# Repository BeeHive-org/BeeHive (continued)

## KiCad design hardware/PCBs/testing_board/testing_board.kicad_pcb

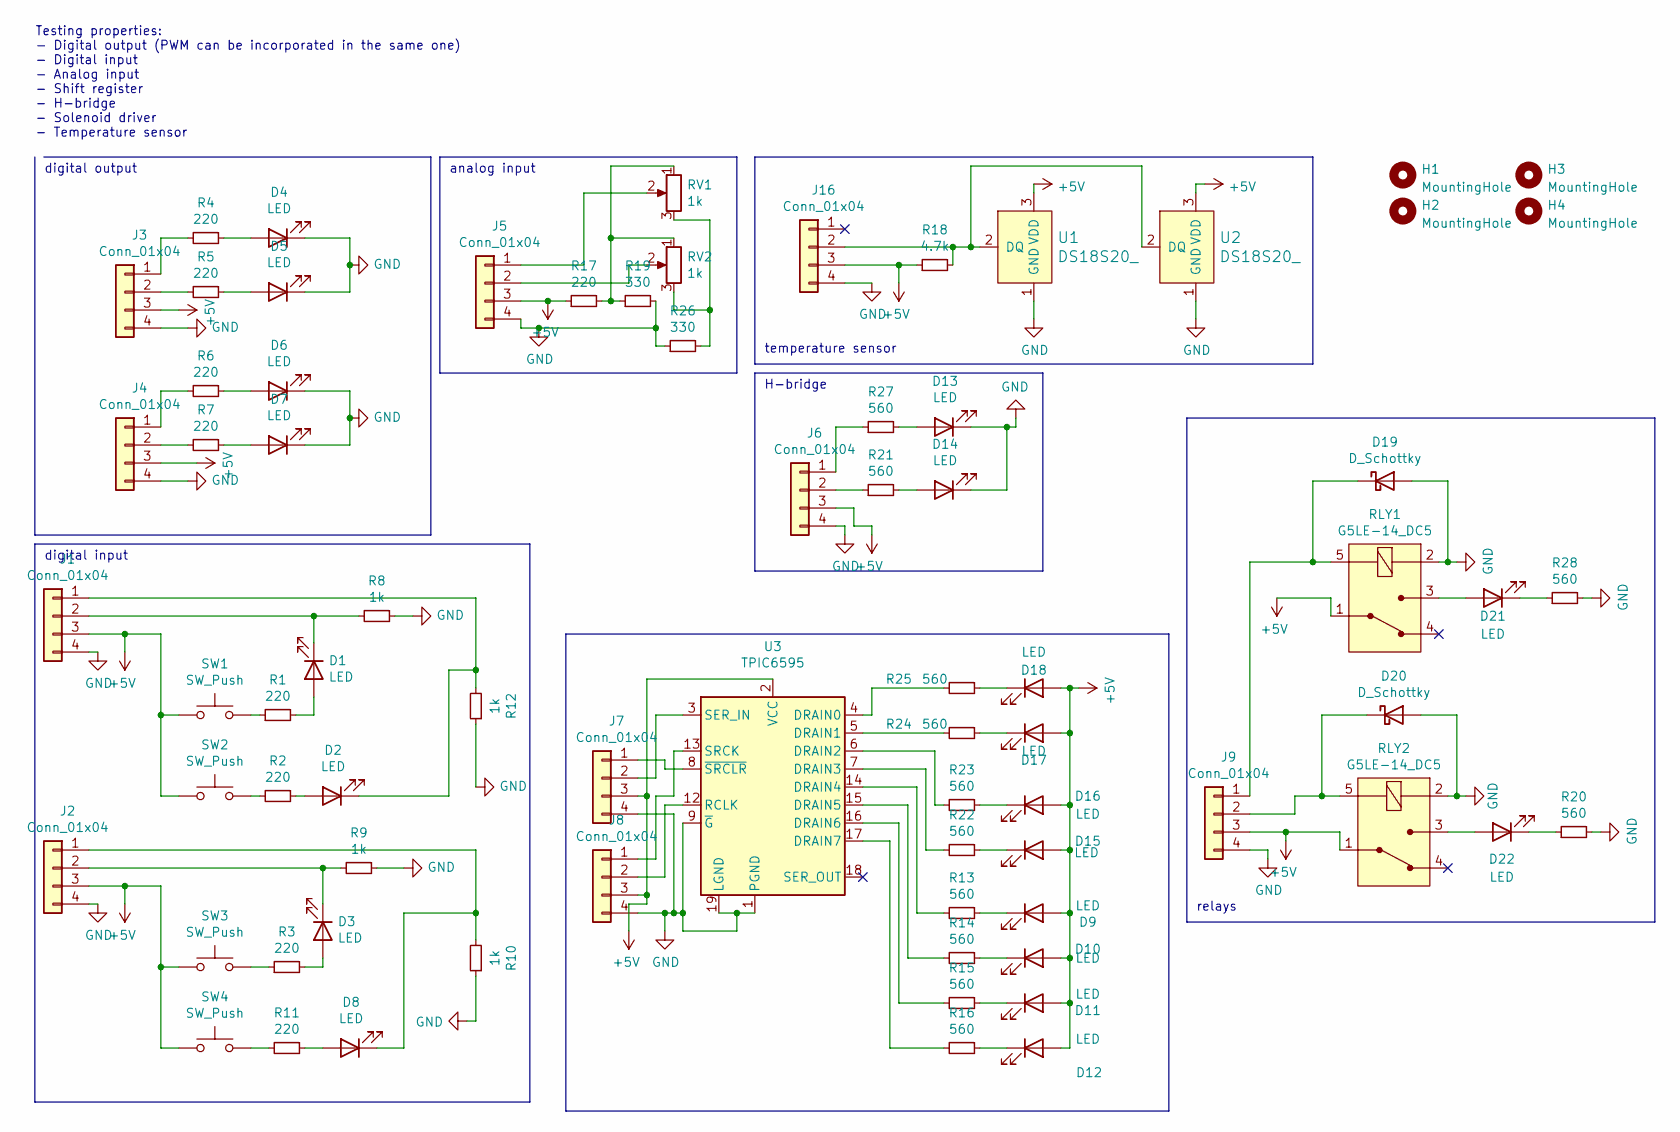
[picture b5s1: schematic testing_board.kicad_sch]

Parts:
D1, D2, D3, D4, D5, D6, D7, D8, D9, D10, D11, D12, D13, D14, D15, D16, D17, D18, D21, D22: LED; LED_D3.0mm
D19, D20: D_Schottky; D_DO-201AE_P15.24mm_Horizontal
H1, H2, H3, H4: MountingHole; MountingHole_3.2mm_M3_DIN965
J1, J2, J3, J4, J5, J6, J7, J8, J9, J16: Conn_01x04; JST_XH_B4B-XH-A_1x04_P2.50mm_Vertical
R1, R2, R3, R4, R5, R6, R7, R11, R17: 220; R_Axial_DIN0204_L3.6mm_D1.6mm_P2.54mm_Vertical
R8, R9, R10, R12: 1k; R_Axial_DIN0204_L3.6mm_D1.6mm_P2.54mm_Vertical
R13, R14, R15, R16, R20, R21, R22, R23, R24, R25, R27, R28: 560; R_Axial_DIN0204_L3.6mm_D1.6mm_P2.54mm_Vertical
R18: 4.7k; R_Axial_DIN0204_L3.6mm_D1.6mm_P2.54mm_Vertical
R19, R26: 330; R_Axial_DIN0204_L3.6mm_D1.6mm_P2.54mm_Vertical
RLY1, RLY2: G5LE-14_DC5; Relay_THT_G5LE-14; MPN G5LE-14 DC5; Digi-Key_PN Z1011-ND
RV1, RV2: 1k; Potentiometer_Alps_RK09K_Single_Vertical
SW1, SW2, SW3, SW4: SW_Push; SW_PUSH_6mm
U1, U2: DS18S20_; TO-92-3; MPN DS18S20+; Digi-Key_PN DS18S20+-ND
U3: TPIC6595; DIP-20_W7.62mm_LongPads

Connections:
+5V: D9.2 (A), D10.2 (A), D11.2 (A), D12.2 (A), D15.2 (A), D16.2 (A), D17.2 (A), D18.2 (A), J1.3, J2.3, J3.3, J4.3, J5.3, J6.3, J7.3, J8.3, J9.3, J16.3, R17.1, R18.1, RLY1.1 (COM), RLY2.1 (COM), SW1.1, SW2.1, SW3.1, SW4.1, U1.3 (VDD), U2.3 (VDD), U3.2 (VCC)
GND: D4.1 (K), D5.1 (K), D6.1 (K), D7.1 (K), D13.1 (K), D14.1 (K), D19.2 (A), D20.2 (A), J1.4, J2.4, J3.4, J4.4, J5.4, J6.4, J7.4, J8.4, J9.4, J16.4, R8.1, R9.1, R10.1, R12.1, R19.2, R20.2, R26.1, R28.2, RLY1.2 (COIL), RLY2.2 (COIL), U1.1 (GND), U2.1 (GND), U3.1 (PGND), U3.9 (~G), U3.10 (PGND), U3.11 (PGND), U3.19 (LGND), U3.20 (PGND)
unnamed: D1.1 (K), J1.2, R8.2
unnamed: D1.2 (A), R1.2
unnamed: D2.1 (K), J1.1, R12.2
unnamed: D2.2 (A), R2.1
unnamed: D3.1 (K), J2.2, R9.2
unnamed: D3.2 (A), R3.2
unnamed: D4.2 (A), R4.1
unnamed: D5.2 (A), R5.1
unnamed: D6.2 (A), R6.1
unnamed: D7.2 (A), R7.1
unnamed: D8.1 (K), J2.1, R10.2
unnamed: D8.2 (A), R11.1
unnamed: D9.1 (K), R13.1
unnamed: D11.1 (K), R15.1
unnamed: D13.2 (A), R27.2
unnamed: D14.2 (A), R21.2
unnamed: D15.1 (K), R22.1
unnamed: D16.1 (K), R23.1
unnamed: D17.1 (K), R24.1
unnamed: D19.1 (K), J9.1, RLY1.5 (COIL)
unnamed: D20.1 (K), J9.2, RLY2.5 (COIL)
unnamed: D21.1 (K), R28.1
unnamed: D21.2 (A), RLY1.3 (NO)
unnamed: D22.1 (K), R20.1
unnamed: D22.2 (A), RLY2.3 (NO)
unnamed: J3.1, R4.2
unnamed: J3.2, R5.2
unnamed: J4.1, R6.2
unnamed: J4.2, R7.2
unnamed: J5.1, RV1.2
unnamed: J5.2, RV2.2
unnamed: J6.1, R27.1
unnamed: J6.2, R21.1
unnamed: J7.1, U3.8 (~SRCLR)
unnamed: J7.2, U3.3 (SER_IN)
unnamed: J8.1, U3.13 (SRCK)
unnamed: J8.2, U3.12 (RCLK)
unnamed: J16.2, R18.2, U1.2 (DQ), U2.2 (DQ)
unnamed: R1.1, SW1.2
unnamed: R2.2, SW2.2
unnamed: R3.1, SW3.2
unnamed: R11.2, SW4.2
unnamed: D10.1 (K), R14.1
unnamed: D12.1 (K), R16.1
unnamed: R17.2, R19.1, RV1.1, RV2.1
unnamed: R24.2, U3.5 (DRAIN1)
unnamed: D18.1 (K), R25.1
unnamed: R26.2, RV1.3, RV2.3
unnamed: R25.2, U3.4 (DRAIN0)
unnamed: R23.2, U3.6 (DRAIN2)
unnamed: R22.2, U3.7 (DRAIN3)
unnamed: R13.2, U3.14 (DRAIN4)
unnamed: R14.2, U3.15 (DRAIN5)
unnamed: R15.2, U3.16 (DRAIN6)
unnamed: R16.2, U3.17 (DRAIN7)

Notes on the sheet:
digital output
analog input
Testing properties: - Digital output (PWM can be incorporated in the same one) - Digital input - Analog input - Shift register - H-bridge - Solenoid driver - Temperature sensor
H-bridge
relays
digital input
temperature sensor

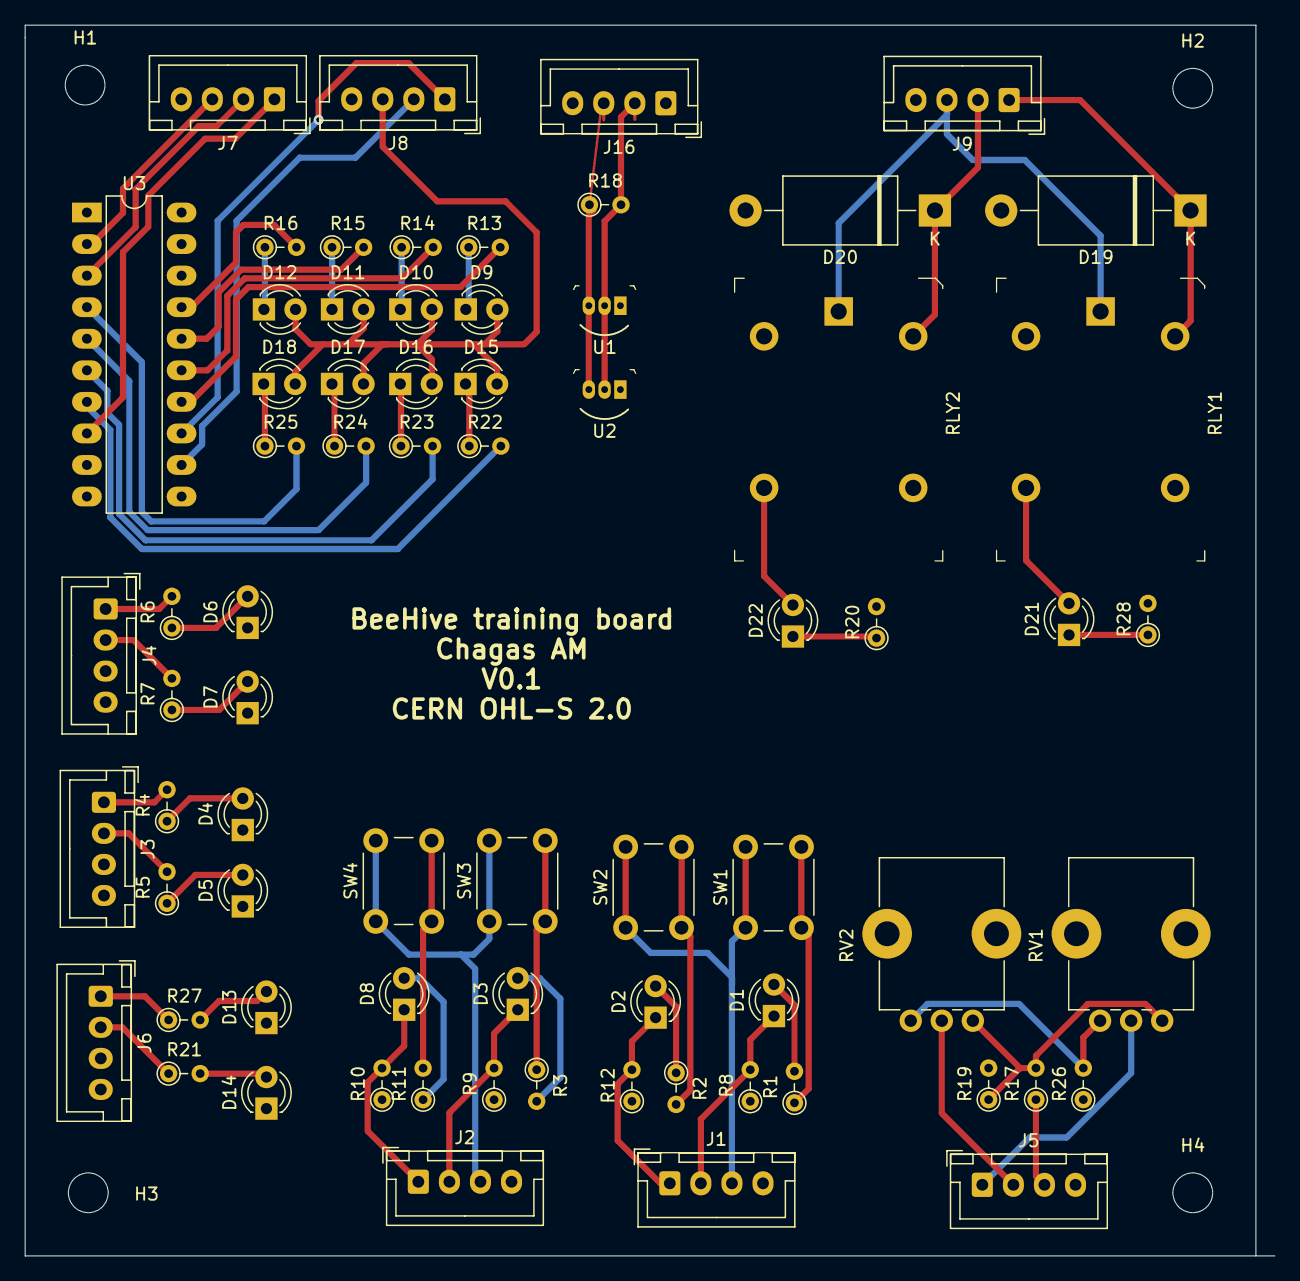
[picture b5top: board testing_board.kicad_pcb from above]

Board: 2 copper layers, 100.6 x 99.1 mm, 75 parts (0 on the bottom side), 57 nets.

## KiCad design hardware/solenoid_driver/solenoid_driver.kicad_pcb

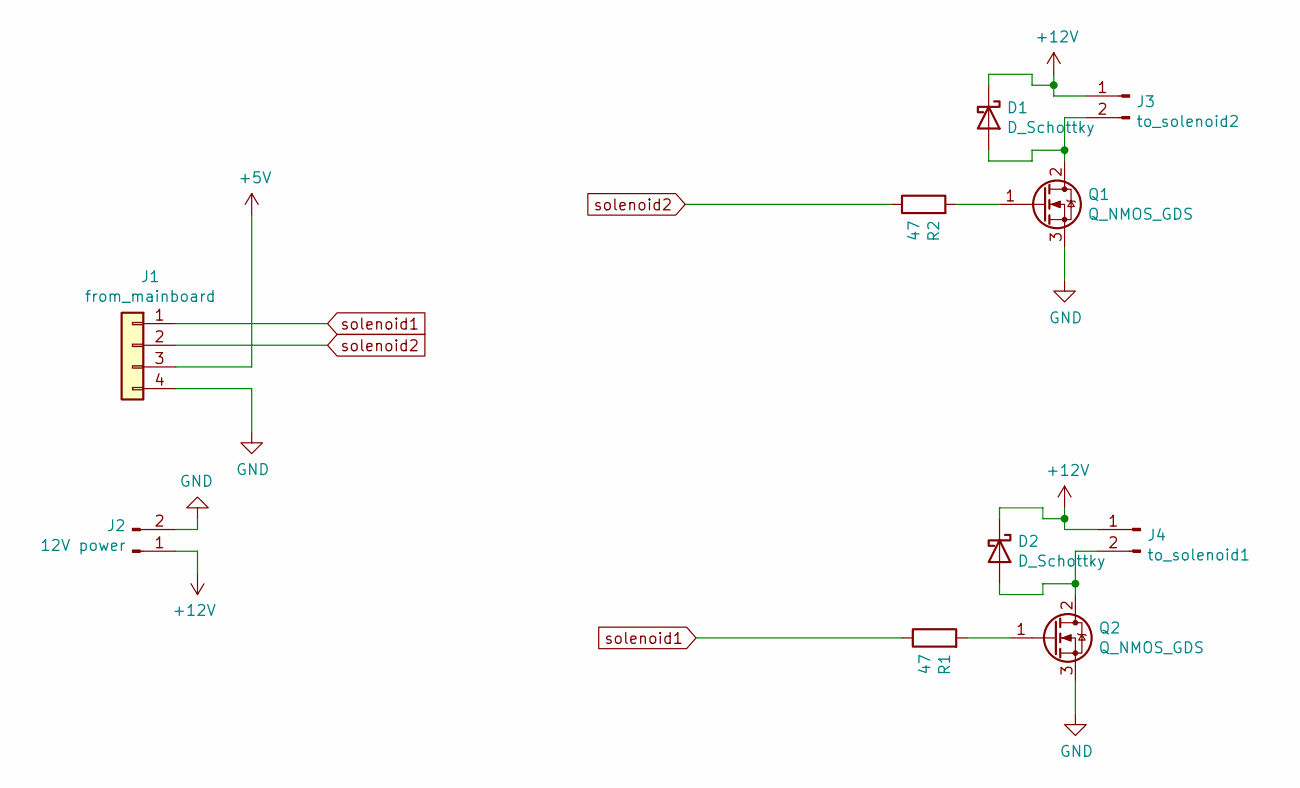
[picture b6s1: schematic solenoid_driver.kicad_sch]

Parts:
D1, D2: D_Schottky; D_DO-201AD_P15.24mm_Horizontal
J1: from_mainboard; JST_XH_B4B-XH-A_1x04_P2.50mm_Vertical
J2: 12V power; JST_XH_B2B-XH-A_1x02_P2.50mm_Vertical
J3: to_solenoid2; JST_XH_B2B-XH-A_1x02_P2.50mm_Vertical
J4: to_solenoid1; JST_XH_B2B-XH-A_1x02_P2.50mm_Vertical
Q1, Q2: Q_NMOS_GDS; TO-220-3_Vertical
R1, R2: 47; R_Box_L13.0mm_W4.0mm_P9.00mm

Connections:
+5V: J1.3
+12V: D1.1 (K), D2.1 (K), J2.1, J3.1, J4.1
GND: J1.4, J2.2, Q1.3 (S), Q2.3 (S)
unnamed: D1.2 (A), J3.2, Q1.2 (D)
unnamed: D2.2 (A), J4.2, Q2.2 (D)
unnamed: Q1.1 (G), R2.2
unnamed: Q2.1 (G), R1.2
solenoid1: J1.1, R1.1
solenoid2: J1.2, R2.1

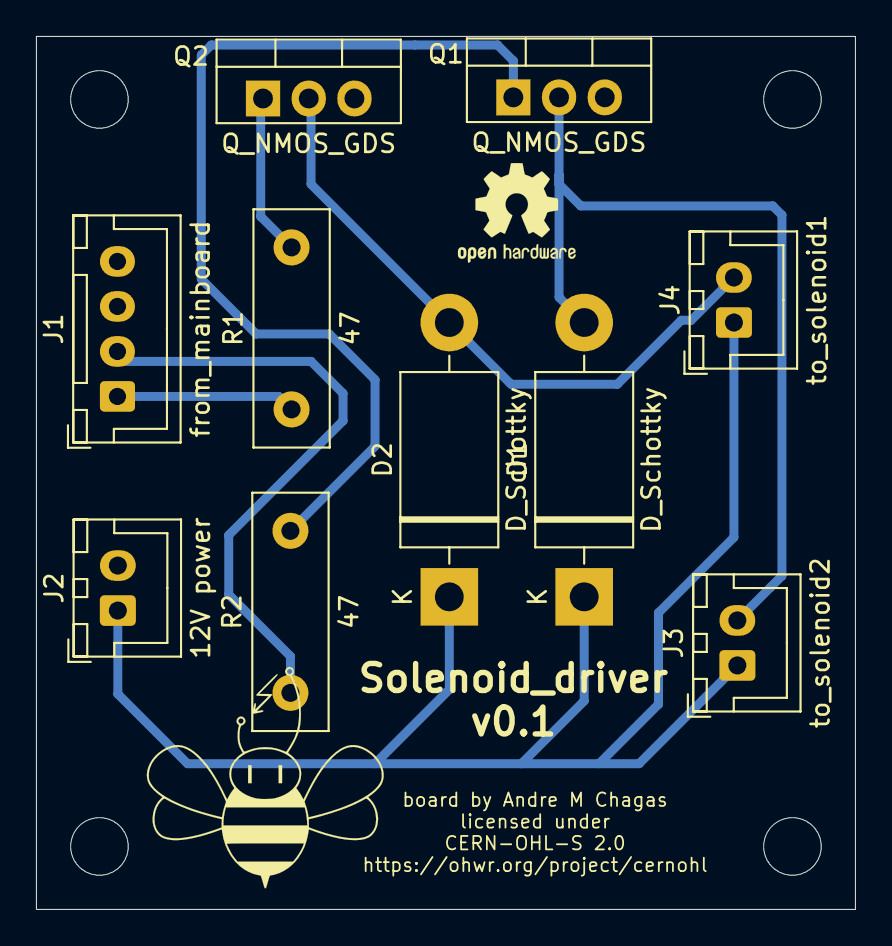
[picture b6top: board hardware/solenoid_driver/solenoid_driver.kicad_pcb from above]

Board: 2 copper layers, 45.5 x 48.5 mm, 10 parts (0 on the bottom side), 8 nets.

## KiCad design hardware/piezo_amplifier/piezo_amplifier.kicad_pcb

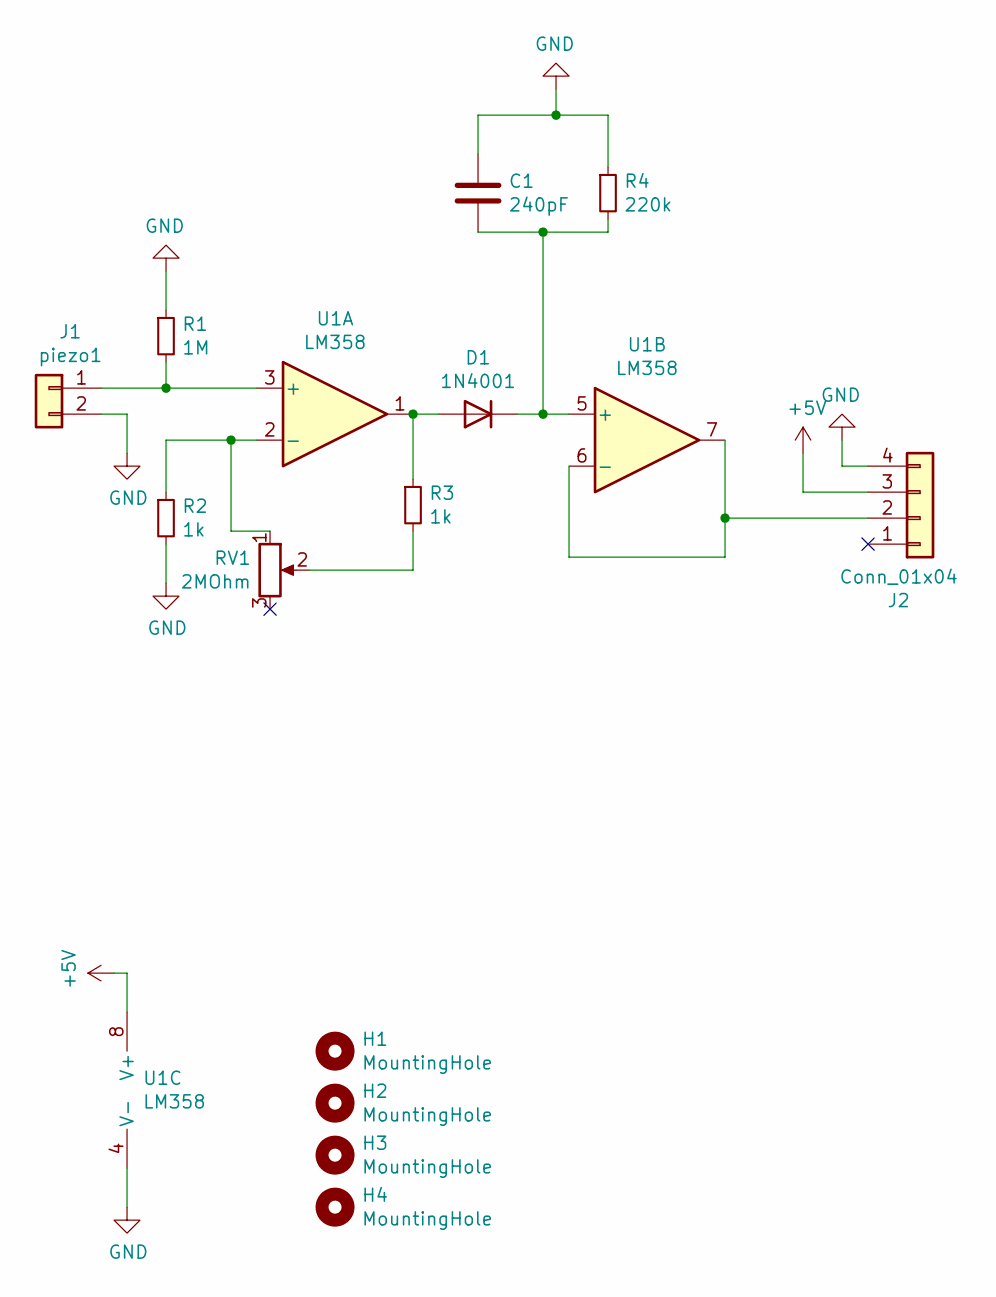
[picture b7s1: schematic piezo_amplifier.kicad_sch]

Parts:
C1: 240pF; C_Disc_D4.7mm_W2.5mm_P5.00mm
D1: 1N4001; D_DO-41_SOD81_P10.16mm_Horizontal
H1, H2, H3, H4: MountingHole; MountingHole_3.2mm_M3_ISO7380
J1: piezo1; JST_XH_B2B-XH-A_1x02_P2.50mm_Vertical
J2: Conn_01x04; JST_XH_B4B-XH-A_1x04_P2.50mm_Vertical
R1: 1M; R_Axial_DIN0204_L3.6mm_D1.6mm_P5.08mm_Vertical
R2, R3: 1k; R_Axial_DIN0204_L3.6mm_D1.6mm_P5.08mm_Vertical
R4: 220k; R_Axial_DIN0204_L3.6mm_D1.6mm_P5.08mm_Vertical
RV1: 2MOhm; JST_XH_B3B-XH-A_1x03_P2.50mm_Vertical
U1: LM358; DIP-8_W7.62mm_LongPads

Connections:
+5V: J2.3, U1.8 (V+)
GND: C1.1, J1.2, J2.4, R1.1, R2.2, R4.1, U1.4 (V-)
unnamed: C1.2, D1.1 (K), R4.2, U1.5 (+)
unnamed: D1.2 (A), R3.1, U1.1
unnamed: J1.1, R1.2, U1.3 (+)
unnamed: J2.2, U1.6 (-), U1.7
unnamed: R2.1, RV1.1, U1.2 (-)
unnamed: R3.2, RV1.2

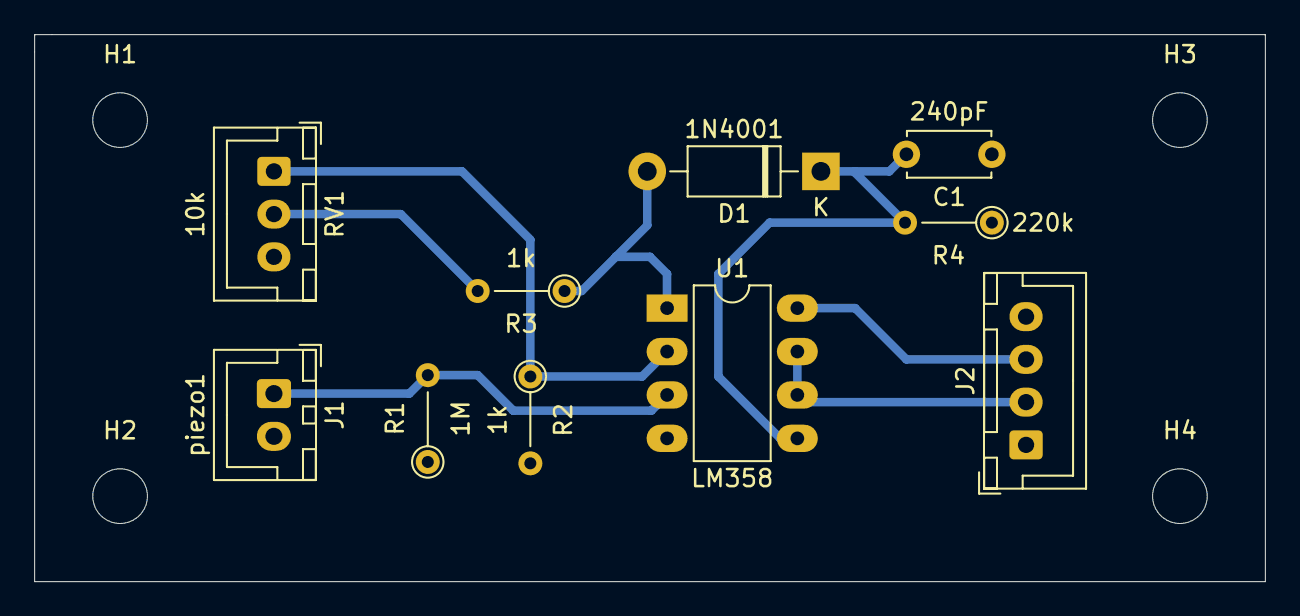
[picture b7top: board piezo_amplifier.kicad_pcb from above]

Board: 2 copper layers, 72.0 x 32.0 mm, 14 parts (0 on the bottom side), 8 nets.

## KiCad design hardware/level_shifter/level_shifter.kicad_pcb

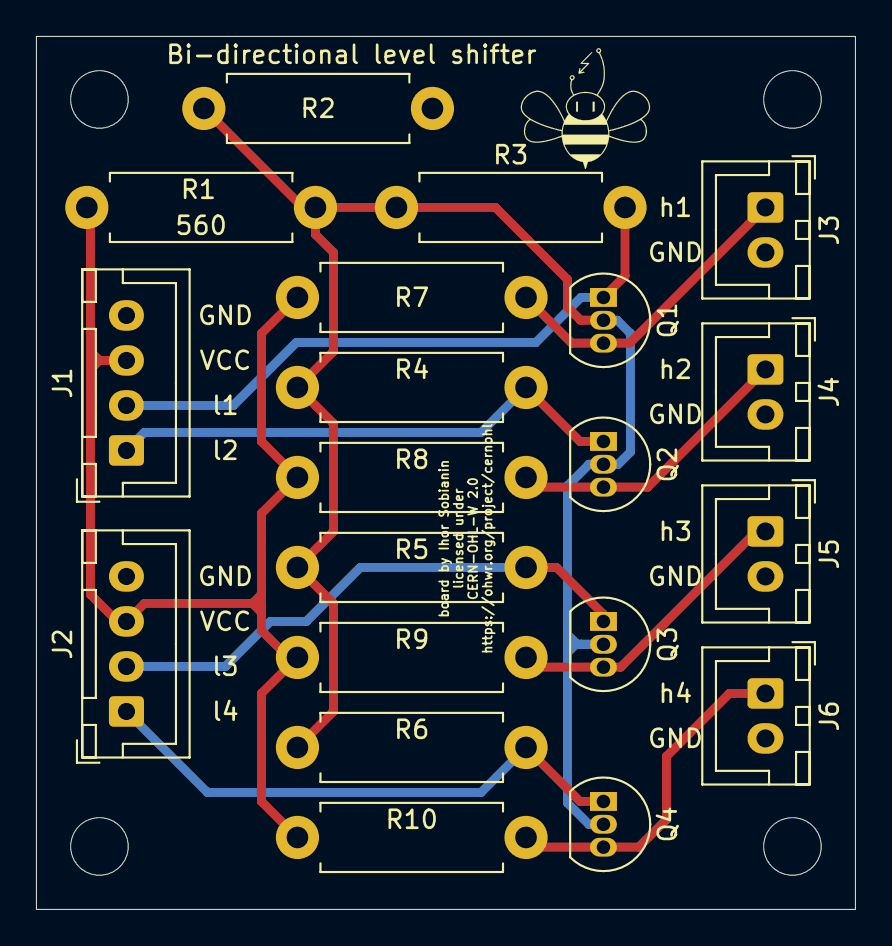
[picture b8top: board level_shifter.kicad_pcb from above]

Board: 2 copper layers, 45.5 x 48.5 mm, 20 parts (0 on the bottom side), 11 nets.

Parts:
J1, J2: Conn_01x04; JST_XH_B4B-XH-A_1x04_P2.50mm_Vertical
J3, J4, J5, J6: Conn_01x02; JST_XH_B2B-XH-A_1x02_P2.50mm_Vertical
Q1, Q2, Q3, Q4: 2N7000; TO-92_Inline
R1: 560; R_Axial_DIN0411_L9.9mm_D3.6mm_P12.70mm_Horizontal
R2, R3, R4, R5, R6, R7, R8, R9, R10: 1k; R_Axial_DIN0411_L9.9mm_D3.6mm_P12.70mm_Horizontal

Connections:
+3V3: Q1.2, Q2.2, Q3.2, Q4.2, R1.1, R2.2, R3.1, R4.1, R5.1, R6.1
+5V: J1.3, J2.3, R1.2, R7.1, R8.1, R9.1, R10.1
GND: J1.4, J2.4, J3.2, J4.2, J5.2, J6.2, R2.1
d1_h: J3.1, Q1.3, R7.2
d1_l: J1.2, Q1.1, R3.2
d2_h: J4.1, Q2.3, R8.2
d2_l: J1.1, Q2.1, R4.2
d3_h: J5.1, Q3.3, R9.2
d3_l: J2.2, Q3.1, R5.2
d4_h: J6.1, Q4.3, R10.2
d4_l: J2.1, Q4.1, R6.2

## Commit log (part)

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2019-11-17 add bare minimum readme
2019-11-17 Create LICENSE
2020-01-16 Schematics for the hub
2020-01-16 PCB file and cache library for schematics
2020-01-16 Other components from FlyPi
2020-01-16 The footprint for the ESP32 DevKit V2
2020-01-17 Gerber files for manufacturing
2020-01-17 Now Kitspace shows PCB correctly
    I could not figure out why the PCB was yellow. All zones were filled with yellow and the silk text was not visible. Looked horrible. However, other viewers worked correctly (used oshpark.com viewer).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
2020-01-23 Added more information regarding connector pinout
2020-01-25 Changed pinout to VCC-GND
2020-06-04 initial explanation on task
2020-06-04 correct bullet points
2020-06-04 finish first draft of the readme for software
2020-06-04 first micropython implementation
2020-06-05 more work on the microcontroller code, and open sound comm
2020-06-11 more software testing, and adding libraries
2020-06-11 organize folders
2020-06-12 work a bit on pin documentation
2020-06-15 more work on basis code
2020-06-16 first working version with output from ESP32 to Bonsai. Digital inputs only
2020-06-29 Redesigned version of the main hub
2020-06-30 work on documentation and on the first task (at the moment designed for the olfactory stimulator)
2020-07-13 more work on serial comm and the olfactory stimulator
2020-07-20 update code with more generic classes
    Instead of creating classes for each use case, we should add "generic" classes that different users can easily adapt for their own use cases.
2020-07-20 more work on base code
2020-07-21 blacken the code style and work on tasks
2020-07-21 solved tasks bugs
2020-07-21 re order repo and add bonsai min example
2020-08-21 update power supply
2020-08-21 move older board versions to archive folder
2020-08-21 update temp/humid sensor
2020-08-21 update gas sensor
2020-08-21 update v3 4 switch array
2020-08-21 update central hub silk --> channel names
2020-09-28 update 1-click boms
2020-10-16 Update PCB files
2020-10-17 Update silk layer
2020-10-18 Add custom libraries
    Add custom schematic symbols, footprints and 3D models
2020-10-18 Quick pinout fix for Peltier driver
    Simple fix with pinout now being correct
2020-11-06 New PID code for testing
    Added new PID control based on Arduino Python code
2020-12-04 update temperature sensor code, add another PID sample and add test code
2020-12-04 update test code
2020-12-09 more work on the PID controller. refactored Ihor's code so that it is a class and it does not need arrays to work.
2020-12-11 Update on 12V5A system power line
    - 12V5A power line is now represented by two connectors with 2 pins across all the modules
    - all .png previews are updated. The central hub now has previews for schematics, PCB tracing and 3D model
    - peltier module now has two 12V5A connectors with redesigned one side of the bridge. Now all MOSFETs can be equipped with heatsinks
    - hum/temp sensor now has its connector position reversed to mimic Grove's one
    - hum/temp and gas sensors now have a small BeeHive logo on front layer rather than one big on back layer
    - hum/temp sensor now use only one layer for signals and one layer for ground
2020-12-17 Add high power LED switch draft
    A rough draft of what is coming. The schematics includes MOSFETS with drivers and all complementary components
2020-12-19 Add high power switch and change 4 switch array
    - added high power switch
    - removed shift register from 4 switch array
    - changed some references on silk layer
    - small changes in switch arrays' tracing (width and paths)
2021-02-20 Add version number to boards
    Add version number to boards and update screenshots, zip gerber archives
2021-04-14 add yaml file to add boards to kitspace. starting with four boards for testing
2021-04-14 add kitspace.yaml
2021-04-14 Add eda fields to kitspace yaml
    This is to work around an issue with finding the kicad_pcb for multi
    projects on Kitspace
2021-04-14 add items to ho led board 1-click-bom.csv file
2021-04-16 the central hub pcb 1-clickbom file had items from Flypi. this commit removes them and removes duplication from 1-clickbom.csv and 1-clickbom.tsv
2021-04-16 Add readme path to kitspace.yaml
2021-04-19 Fix some images in readme
2021-04-19 update 1 click boms
2021-04-20 fix 1-click-bom hp led switch
2021-05-17 Add driver board
    Driver board is a next iteration of peltier board
2021-05-17 Add gerbers and change BOM
2021-05-20 Update driver board
    Driver board v0.1
    Apart from removing temperature sensor connector, there are some minor changes:
    - some tracks, such as 12V line near Q1 and Q3, were changed;
    - 12V connectors are now moved to the "front panel" of the board.
2021-05-20 Update screenshots
2021-05-20 Update file
2021-05-24 Add spike and hold board with boost converter
2021-05-25 Add discrete boost converter
2021-05-25 Update boost converter
2021-05-26 Rearrange folders
2021-05-28 Make inductor's footprint unified across system
    Now all inductors have the same footprint and component.
    Some minor changes in silk layers: added values to resistors and arranged them in a more readable way
2021-06-19 Add temperature sensor breakout board
2021-06-19 Add screenshots
2021-06-28 organize folders, create zip for temp sensor gerber
2021-06-28 Update kitspace.yaml
    remove peltier board from kitspace as this is now a legacy board
2021-07-10 Add level shifter
    Add level shifter schematics and PCB
2021-07-11 Add gerbers and screenshots
    Added gerber files, screenshots and updated silkscreen
2021-07-31 Add a draft of an IR transmitter/receiver
2021-08-01 Add IR sensor/transmitter
2021-08-07 Add improved version of IR transmitter/receiver
2021-08-13 Add adaptor
2021-08-13 Add PCB and screenshots
2021-08-14 Add panelised grove adaptor
    Panelised version of the grove adaptor. It features an 4x3 array of adaptors so it is cheaper to manufacture them and more convenient to order
2021-10-06 first schematics for the testing board
2021-10-09 Add v0.3 switch array
    Previous version was based on a low-current shift register which could not possibly work in the given scenario. It is switched to a more powerful IC
2021-10-14 Add ESP32 5V trace and minor changes
    ESP32 is now connected to the same line as Raspberry Pi that should reduce the noise.
    Add new screenshot to the temperature breakout board
2021-10-22 Apply CERN-W license
    Apply CERN-W license to all boards, move the first iteration of the IR_sensor to the archive
2021-10-22 clean up repo
2021-10-22 finish schematics of test board
2021-10-22 more work on testing board
2021-10-25 fix broken file
2021-12-02 Update HP switch
    Update wrong tracing and connections on HP switch
2021-12-07 update testing board
2022-01-13 rename some folders
2022-01-13 add more media
2022-01-13 more media
2022-01-15 modify central hub according to 'review boards issue' and add some media files
2022-01-16 boards review
2022-01-16 correct folder name
2022-01-16 update some boards so that they get properly loaded be the manufacturer system
2022-01-17 add gerbder
2022-01-17 update grove panel to comply with manufacturer request
2022-01-19 Add USB footprint to 5V power supply
    Add USB footprint to the 12V to 5V converter. It is a continuation of the idea to free space on the main hub because of USB irrelevancy there
2022-02-05 Add enclosure
    First iteration of a modular enclosure for BeeHive. Some parts are hollowed out to make them easier to print. However, it is still work-in-progress version
2022-02-11 Update enclosure
    - Change shape of the ,ain support from circle to triangle for easier 3D printing
    - Increase tolerances
    - Make PCB cover more rigid and add missing middle line with rails
    - Increase height of internal and main supports
2022-02-25 Update enclosure
2022-03-11 make gerber files
2022-03-14 update testing board and start work on piezo amplifier
2022-03-25 prototype zero for piezo amplifier
2022-04-13 update piezo amplifier
2022-05-17 add some media, solenoid driver update
2022-05-23 update to92 connector in level shifter
    it is now a wide footprint, which should be easier to solder
2022-05-23 save the level shifter update also for the schematics
2022-06-25 Serial library
2022-06-25 Rename README.md.txt to README.md
2022-06-25 fixed
2022-07-02 open sound coms update
2022-07-29 Add mounting holes and spacers
2022-07-30 update training bpoard design
2022-08-02 update solenoid driver and training board
2022-08-02 update training board
2022-08-05 Update IR sensor
    MOSFET was wrongly connected to the LED thus rendering the PCB unusable. Now, it is connected the right way
2022-08-24 example 1 for solenoid driver
2022-09-12 Update example1.py
    example to use solenoid driver
2022-09-12 update piezo amp.
2022-09-13 update workshop folder
2022-09-21 update piezo amplfier
2022-09-21 update 1 click bom
2022-09-21 update things for the course
2022-10-31 work on training board updates
2022-11-07 update testing board and its bom
2022-11-08 testing gh
2022-11-09 Update README.md
    add correct location
2022-11-14 add workshop materials
2022-11-15 add code for the course
2022-11-17 workshop code
2022-11-23 Bonsai OSC to esp32
2022-11-23 reorganise serial triggering to bonsai workflows
2022-11-23 update archive code
2022-11-24 organise repo and start adding boards to kicad
2022-11-25 add relative readme for 8 switch array board
2022-11-25 update testing to training board
2022-12-07 changed to bonsai 2.7
2022-12-07 deleting replicated files on the wrong place
2022-12-07 fix gitignore files
2022-12-07 fix .gitignore
2022-12-29 Fix the rest of `gerber` paths
2023-02-07 client test for receiveing bundles
2023-02-13 update solenoid driver gerber
2023-02-23 Bundle Test
2023-02-23 bring esp32osc readme to right folder
2023-02-23 Server: New passes template, new bundle
2023-02-23 bonsai client
2023-02-24 Add PCB holder
    Simple PCB 3d printable holder. Comes with a fully parametrised FreeCAD file
2023-03-02 remove archive folder
2023-03-02 move things to new folders and write about naming conventions
2023-03-09 update OSC library from Spotlightkid newest version
2023-03-09 Work in progrees for upython receive osc messages on esp32
2023-03-09 Update IR sensor to v0.4
    IR sensor board updated to version 0.4:
    - removed MOSFET switch;
    First of all, it was supposed to be IRFL44 , L version which can be used with logic levels. But instead we put IRFZ which barely opens at 3.3 V and thus cannot be effectively used here. Moreover, dur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
    - Add additional phototransistor connector
    - Add additional IR LED connector
2023-03-10 Add v0.2 version of the training board
    New v0.2 version of the training board:
    - added rotary encoder
    - removed one of relays
    - fixed wiring on potentiometers
    - removed h-bridge LEDs
    - added module to demonstrate how jumper wires work
2023-03-24 First working test sending OSC data from Bonsai->esp32
2023-03-30 trying to define dispatch function
2023-05-03 Add v2 central board and alternative variant
    New central board:
    - decentralised 5V line that can be turned on/off independently for each connector
    - 12V can be turned on/off by a jumper
    - layout is re-arranged
    - back layer is a solid GND
    An alternative variant has a power jack that is confined by the PCB
2023-05-08 One step further get function calll return data from esp to bonsai
2023-05-08 one small step for mainkind
2023-05-11 Update functionCallTest.py
    add a couple of simple examples on callfunctions
2023-05-12 update manual boot for a faster start
2023-05-17 correct typo
2023-06-01 function return with typped tupples
2024-05-12 remove zips, update training board
2024-07-03 updates that need to be verified in the central board and level shifter
2025-02-10 create folder for paper figures, modify figure 1, start on figure 2
2025-04-29 Add outline to text
2025-04-29 Updated figure
    With text outline and larger numbers
2025-04-29 add workshop information
2025-05-20 Fix grove_adaptor_panel edge cuts (using KiCad 9)
2025-06-25 add figures and prepare things for upcoming figures
2025-06-30 first sketch of maze figure
2025-06-30 update maze image
2025-07-01 update figures, headfixed and maze
2025-08-06 more work on paper figures
2025-09-15 update_paper_figures
2025-09-16 mouse wheel image, plus start of odour stimulator
2025-09-24 add more paper figures
2025-10-01 add figures
2025-10-07 update figures
2025-10-31 version of the stage figure
2025-10-31 update stage figure
2025-11-14 update multiplexor image
2025-11-14 improve multiplexor figure colours
2025-11-14 update mouse wheel figure
2025-11-28 update resolution on figure 1
